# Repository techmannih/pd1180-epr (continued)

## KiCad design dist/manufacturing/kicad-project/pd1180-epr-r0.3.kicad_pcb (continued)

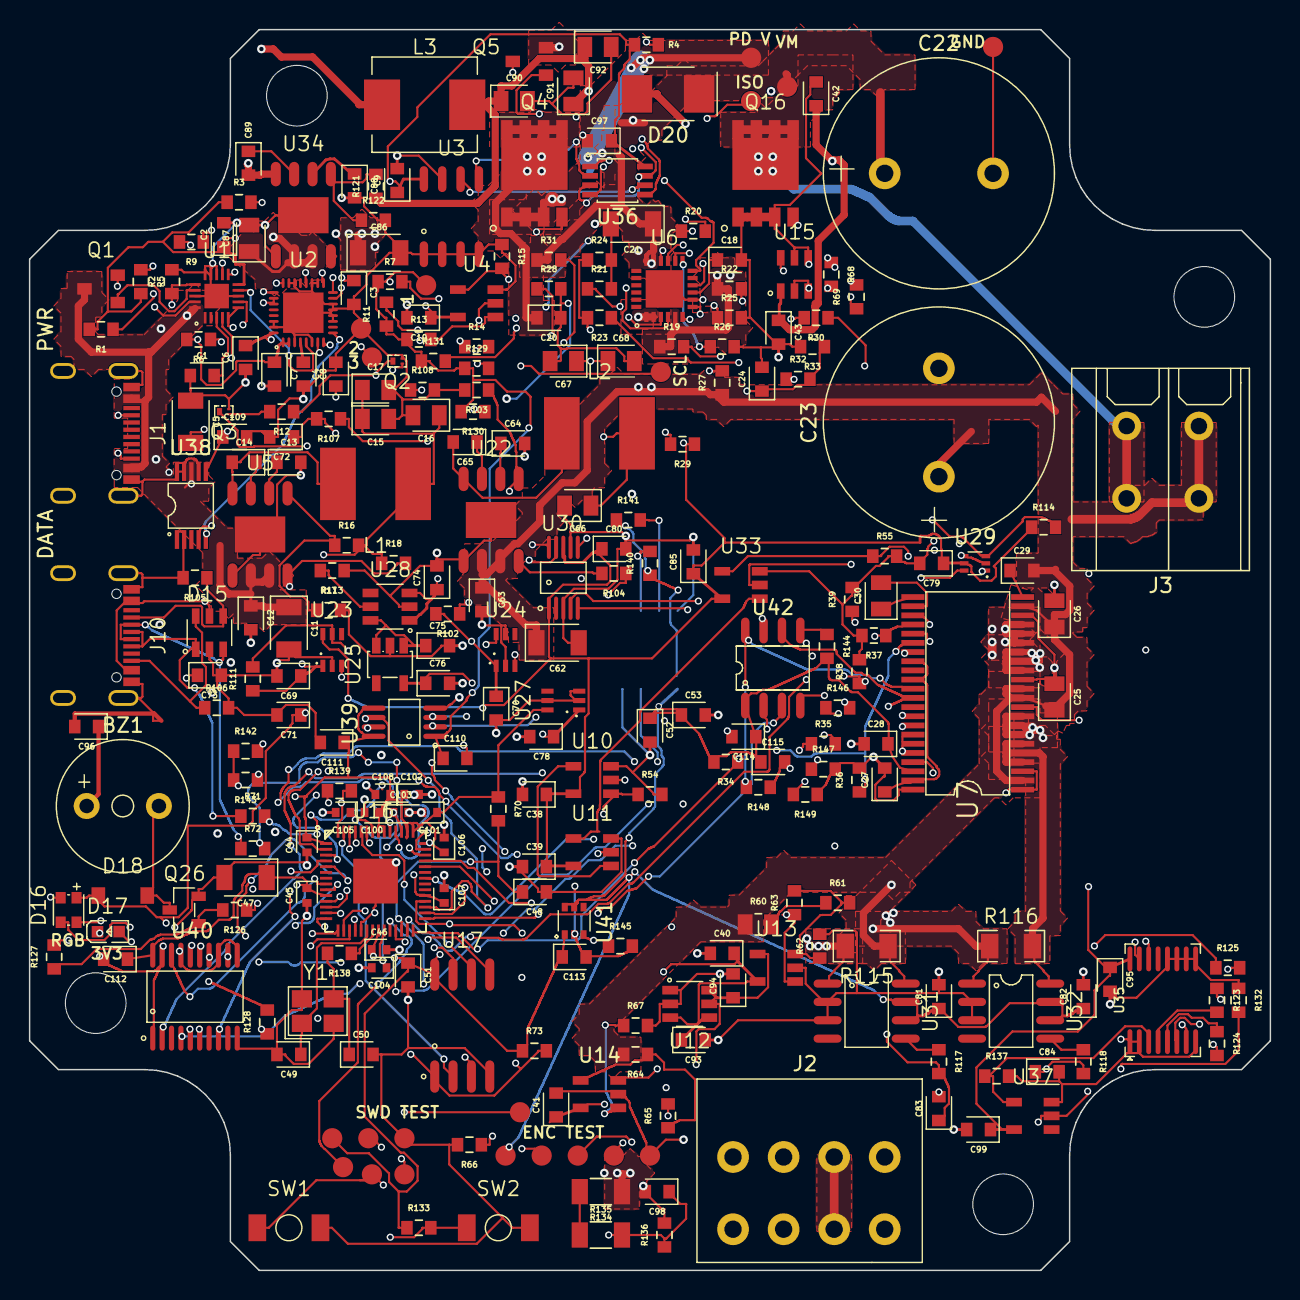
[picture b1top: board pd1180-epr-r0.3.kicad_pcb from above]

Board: 4 copper layers, 85.9 x 85.9 mm, 273 parts (1 on the bottom side), 158 nets.

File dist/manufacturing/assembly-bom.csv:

"Comment","Designator","Footprint","LCSC Part #","Quantity"
"USB4105-GF-A-060","J1,J10","SMD","C3025063","2"
"1M","R107","0603","C22935","1"
"47k","R108,R137","0603","C25819","2"
"100nF","C72,C9,C10,C14,C65,C69,C70,C24,C114,C38,C39,C89,C94,C40,C41,C43,C28,C48,C51,C73,C110,C111,C112,C74,C78,C109,C79,C80,C81,C82,C85,C99,C95,C97","0603","C14663","34"
"TPD4S480RUKR","U1","QFN-20(3x3)","C43131250","1"
"TPS26750SRSMR","U2","VQFN-32-EP(4x4)","C42166327","1"
"BSS123LT1G","Q1,Q5","SOT-23","C78755","2"
"100nF","C1,C12,C63,C20","0603","C15725","4"
"1uF","C2,C13,C64,C18,C115,C88,C93,C42,C27,C29,C113,C75","0603","C15849","12"
"220pF","C3,C4","0603","C106210","2"
"4.7uF","C5,C47","1206","C51205","2"
"10uF","C6,C7,C8,C71,C76,C96","0603","C96446","6"
"10k","R1,R14,R18,R104,R111,R21,R28,R29,R30,R148,R149,R54,R34,R35,R36,R37,R38,R39,R55,R70,R133,R73,R114,R131,R132","0603","C844918","25"
"100k","R2,R11,R13,R15,R16,R102,R121,R67,R69,R145,R113,R127","0603","C25803","12"
"M24512-RMN6TP","U3","SOIC-8","C79991","1"
"4.7k","R3,R4,R5,R6,R7,R22,R140,R141,R142,R143,R144,R128,R129,R130","0603","C23162","14"
"0","R9,R12","0603","C21189","2"
"CSD17484F4","Q2,Q3","PicoStar-3","C2862245","2"
"SN74LVC1G08DBVR","U4,U10,U11,U33","SOT-23-5","C7666","4"
"LMR36510ADDAR","U5,U22,U34","SOP-8-EP","C1858393","3"
"SWPA6045S220MT","L1,L2","SMD,6x6mm","C83454","2"
"2.2uF","C11,C62,C21,C86","1206","C170101","4"
"22uF","C15,C16,C17,C66,C67,C68,C90,C91,C92","0805","C45783","9"
"43.2k","R17,R103","0603","C137720","2"
"LM66100DCKR","U23,U24,U27","SC-70-6","C2869734","3"
"CSD19534Q5A","Q4,Q16","SON-8(5x6)","C114200","2"
"TPS26630RGER","U6","VQFN-24(4x4)","C1850276","1"
"180k","R19,R20,R31,R32","0603","C22827","4"
"422k","R23","0603","C705777","1"
"10k","R24,R62","0603","C95204","2"
"4.99k","R25","0603","C7293210","1"
"20k","R26,R33","0603","C4184","2"
"360k","R27","0603","C23146","1"
"EEUFS1J102","C22,C23","Plugin,D16xL25mm","C407979","2"
"MCP4822-E/SN","U42","SOIC-8","C16040","1"
"1.5k","R146,R147","0603","C22843","2"
"DRV8262DDVR","U7","HTSSOP-44","C33828788","1"
"2601-3104","J2","Plugin,P=3.5mm","C20252915","1"
"SRP7050TA-470M","L3","SMD,7.3x6.6mm","C2047110","1"
"9.09k","R122","0603","C861611","1"
"220nF","C87","0805","C513710","1"
"REF3425IDBVR","U12","SOT-23-6","C187836","1"
"TLV3201AIDBVR","U13,U14","SOT-23-5","C105188","2"
"180k","R60","0805","C351604","1"
"16.2k","R61","0603","C728583","1"
"1M","R63","0603","C326730","1"
"430k","R64","0603","C2984356","1"
"20k","R65","0603","C328424","1"
"1.2k","R66","0603","C5454462","1"
"UCC27511DBVR","U15","SOT-23-6","C191027","1"
"10","R68","0603","C22859","1"
"236-402","J3","Plugin","C3819425","1"
"SS10100","D20","SMBF","C49242208","1"
"4.7k","R134,R135","1206","C6675858","2"
"510","R136","0603","C7468460","1"
"10nF","C98,C83,C84","0603","C57112","3"
"100nF","C25,C26,C30","0805","C28233","3"
"100nF","C107,C106,C108,C100,C101,C104,C105,C44,C45,C46","0402","C1525","10"
"1uF","C102,C103","0402","C52923","2"
"1k","R138,R139,R117,R118,R123,R126","0603","C21190","6"
"RP2040","U16","LQFN-56(7x7)","C2040","1"
"27","R71,R72","0603","C25190","2"
"X322512MSB4SI","Y1","SMD3225-4P","C9002","1"
"33pF","C49,C50","0603","C1663","2"
"TS-1088-AR02016","SW1,SW2","SMD,4x3mm","C720477","2"
"W25Q32JVSSIM","U17","SOIC-8-208mil","C6000508","1"
"5.1k","R105,R106","0603","C23186","2"
"USBLC6-4SC6","D15","SOT-23-6L","C111212","1"
"TCA9517ADGKR","U39","VSSOP-8-0.65mm","C201698","1"
"SN74LVC244APWR","U40","TSSOP-20","C7668","1"
"TPS22919DCKR","U41","SC-70-6","C2149796","1"
"TPS2553DBVR","U28","SOT-23-6","C55266","1"
"TLV75533PDBVR","U25","SOT-23-5","C404027","1"
"TMP102AIDRLR","U29","SOT-563","C99269","1"
"ADS1115IDGSR","U30","VSSOP-10","C37593","1"
"INA237AIDGSR","U38","VSSOP-10-0.5mm","C2864837","1"
"INA240A1DR","U31,U32","SOIC-8","C2060769","2"
"FRM121WFR005TM","R115,R116","1206","C7419996","2"
"PCA9538PWR","U35","TSSOP-16","C201530","1"
"SN74LVC1G17DBVR","U37","SOT-23-5","C7836","1"
"NH-B2020RGBA-HF","D16","SMD,2.1x2.1mm","C2874116","1"
"FMB09A03-3V","BZ1","Plugin,D=9mm","C417385","1"
"AO3400A","Q26","SOT-23","C20917","1"
"XL-1608SURC-06","D17","0603","C965799","1"
"BAV21W-7-F","D18","SOD-123","C155214","1"
"330","R124,R125","0603","C23138","2"
"SN74LVC2G66DCTR","U36","MSOP-8","C2651913","1"

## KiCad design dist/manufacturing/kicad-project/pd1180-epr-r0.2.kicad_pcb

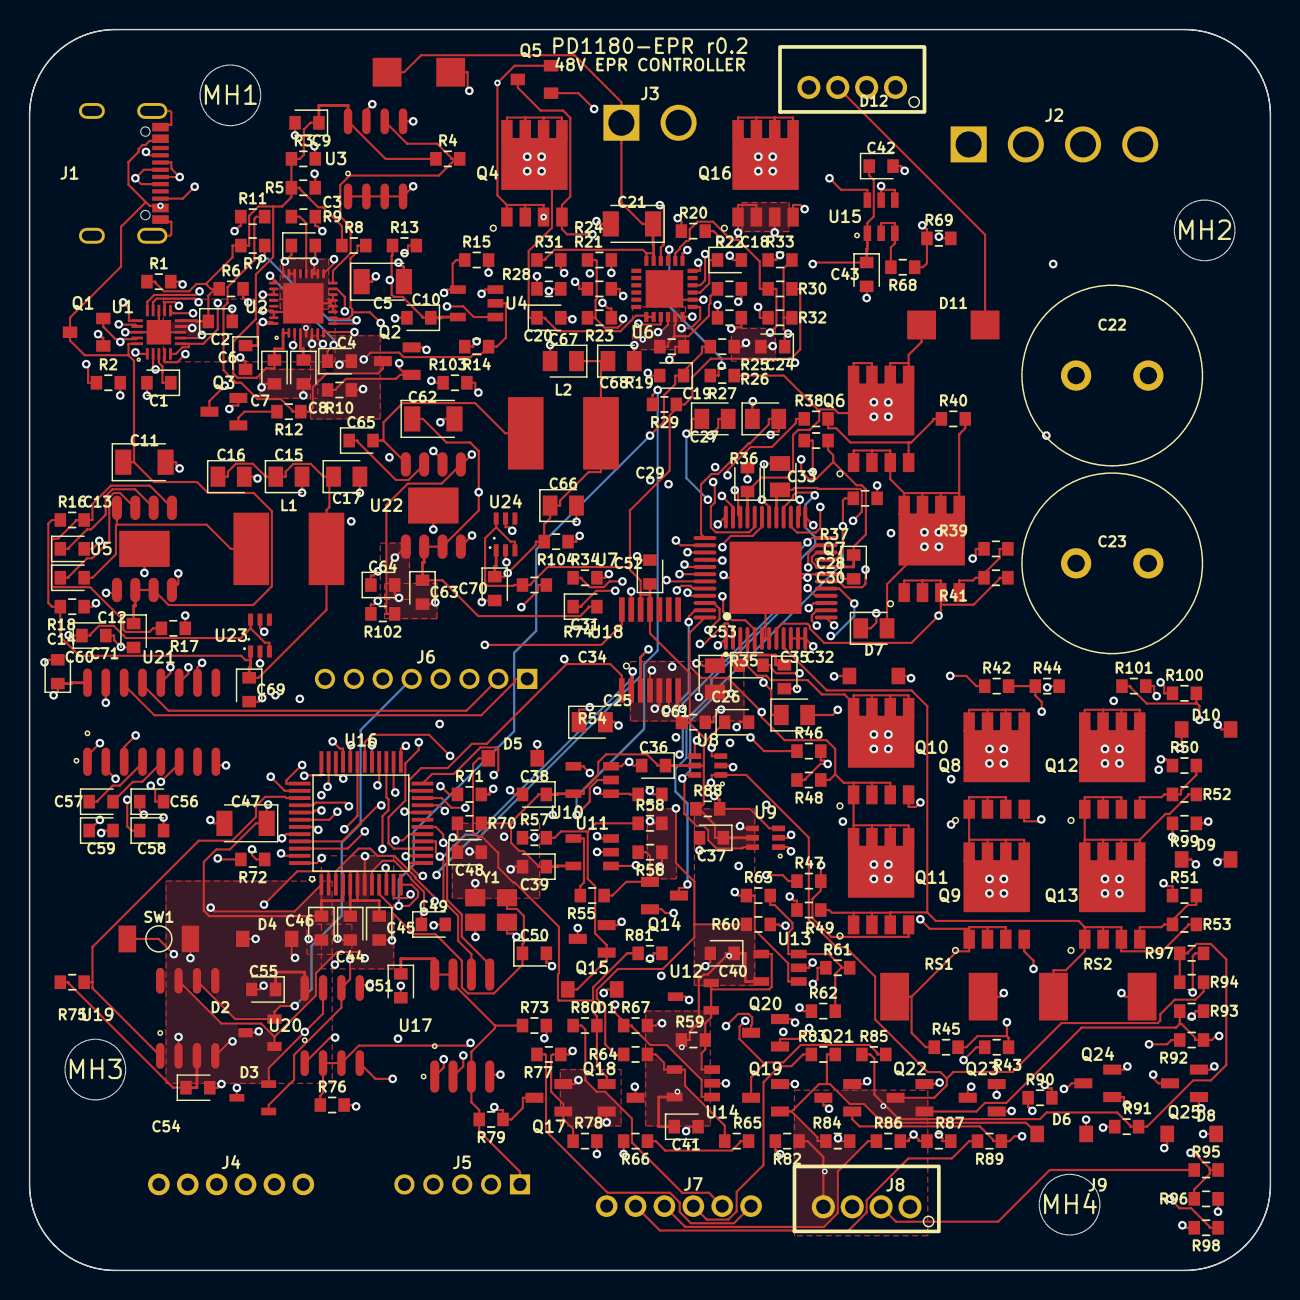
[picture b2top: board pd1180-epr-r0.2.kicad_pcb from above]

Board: 4 copper layers, 85.9 x 85.9 mm, 255 parts (0 on the bottom side), 177 nets.

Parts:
C1, C2, C9, C10, C12, C14, C18, C19, C20, C24, C28, C29, C31, C36, C37, C38, C39, C40, C41, C43, C44, C45, C46, C48, C51, C52, C54, C55, C56, C57, C58, C59, C60, C61, C63, C65, C69, C70: 100nF; capacitor_cap0603
C3, C4: 220pF; capacitor_cap0603
C5, C47: 4.7uF; capacitor_cap1206
C6, C7, C8, C71: 10uF; capacitor_cap0603
C11, C21, C62: 2.2uF; capacitor_cap1206
C13, C42, C53, C64: 1uF; capacitor_cap0603
C15, C16, C17, C66, C67, C68: 22uF; capacitor_cap0805
C22, C23: 470uF; EEUFR1J471
C25: 4.7uF; capacitor_cap0805
C26: 4.7uF; capacitor_cap0603
C27: 470nF; capacitor_cap0805
C30: 22nF; capacitor_cap0805
C32, C33, C34, C35: 220nF; capacitor_cap0805
C49, C50: 12pF; capacitor_cap0603
D1, D4, D5, D6, D7, D8, D9, D10: D; BAV21W-7-F
D2: SM24CANB-02HTG
D3: PSM712-LF-T7
D11, D12: D; SS110
J1: J1; USB4105-GF-A
J2: J2; B4P-VH_LF_SN
J3: J3; B2P-VH_LF_SN
J4: J4; B6B-PH-K-S_LF_SN
J5: J5; B5B-PH-K-S_LF_SN
J6: J6; B8B-PH-K-S_LF_SN
J7: J7; B6B-PH-K-S_LF_SN
J8: J8; B4B-PH-K-S_LF_SN
J9: J9; B4B-PH-K-S_LF_SN
L1, L2: 22µH; SWPA6045S220MT
MH1, MH2, MH3, MH4: hole_circle_holeDiameter4.2mm
Q1, Q5: BSS123LT1G
Q2, Q3, Q14, Q15, Q17, Q18, Q19, Q20, Q21, Q22, Q23, Q24, Q25: MMBT5551LT1G
Q4, Q6, Q7, Q8, Q9, Q10, Q11, Q12, Q13, Q16: CSD19534Q5A
R1, R11, R12, R13, R14, R18, R21, R24, R28, R29, R30, R35, R36, R37, R54, R56, R58, R62, R70, R73, R74, R75, R76, R78, R81, R84, R87, R90, R93, R96, R99, R101, R104: 10kΩ; resistor_res0603
R2, R9, R10, R15, R16, R40, R41, R44, R45, R48, R49, R52, R53, R57, R67, R69, R102: 100kΩ; resistor_res0603
R3, R4, R5, R6, R7, R8, R79, R82, R85, R88, R91, R94, R97: 4.7kΩ; resistor_res0603
R17, R103: 43.2kΩ; resistor_res0603
R19, R20, R31, R32, R60: 180kΩ; resistor_res0603
R22, R59: 220Ω; resistor_res0603
R23, R64: 430kΩ; resistor_res0603
R25: 4.02kΩ; resistor_res0603
R26, R33, R61, R65: 20kΩ; resistor_res0603
R27: 360kΩ; resistor_res0603
R34: 2.2Ω; resistor_res0603
R38, R39, R42, R43, R46, R47, R50, R51, R68: 10Ω; resistor_res0603
R55, R66, R98, R100: 1kΩ; resistor_res0603
R63: 1MΩ; resistor_res0603
R71, R72: 22Ω; resistor_res0603
R77, R80, R83, R86, R89, R92, R95: 47kΩ; resistor_res0603
RS1, RS2: HoLLR2512-3W-33mR-1%; HoLLR2512-3W-33mR-1
SW1: SW1; TS-1088-AR02016
U1: TPD4S480RUKR
U2: TPS26750SRSMR
U3: M24512-RMN6TP
U4, U10, U11: SN74LVC1G08DBVR
U5, U22: LMR36510ADDAR
U6: TPS26631RGER
U7: TMC5160A-TA-T
U8, U9: 74LVC1G157GW,125; 74LVC1G157GW_125
U12: TL431AIDBZR
U13, U14: TLV3201AIDBVR
U15: UCC27511DBVR
U16: STM32G0B1CBT6
U17: W25Q32JVSSIQ
U18: AS5047P-ATSM
U19: TCAN332DR
U20: MAX3485EESA+T; MAX3485EESA_T
U21: MAX3232ESE+T; MAX3232ESE_T
U23, U24: LM66100DCKR
Y1: Y1; X322516MLB4SI

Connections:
BLOCK_FAST_GATE: Q5.1, U6.4
BLOCK_GATE: Q4.4, Q5.3, U6.3
BOOT_A1: C32.1, U7.42
BOOT_A2: C33.1, U7.35
BOOT_B1: C34.1, U7.2
BOOT_B2: C35.1, U7.43
BRAKE_DRIVE: R68.1, U15.2, U15.3
BRAKE_GATE: Q16.4, R68.2, R69.1
BRAKE_MID: R60.2, R61.1
BRAKE_ON: R63.1, U13.1, U15.6
BRAKE_RETURN: J3.2, Q16.5, Q16.6, Q16.7, Q16.8, Q16.9
BRAKE_SENSE: R61.2, R62.1, R63.2, U13.3
BUCK_BOOT: C14.1, U5.7
BUCK_FB: R16.2, R17.1, U5.5
BUCK_SW: C14.2, L1.1, U5.8
BUCK_VCC: C13.1, U5.6
CAN_H: D2.1, J6.4, U19.7
CAN_L: D2.2, J6.5, U19.6
CAN_RX: U16.38, U19.4
CAN_TX: R75.2, U16.39, U19.1
CC1_CONN: J1.15, U1.4, U1.7
CC1_PD: C3.1, U1.12, U2.24
CC2_CONN: J1.9, U1.5, U1.6
CC2_PD: C4.1, U1.11, U2.25
CC_FAULT_N: R1.2, U1.9, U2.5
CC_VBIAS: C1.1, U1.3
DIN0: Q17.3, R79.2, U16.2
DIN0_24V: J7.1, R77.1
DIN0_BASE: D4.1, Q17.1, R77.2, R78.1
DIN1: Q18.3, R82.2, U16.3
DIN1_24V: J7.2, R80.1
DIN1_BASE: D5.1, Q18.1, R80.2, R81.1
DIR_24V: J8.2, R95.1
DIR_IN: Q23.3, R97.2, U9.1, U16.31
DIR_IN_BASE: D10.1, Q23.1, R95.2, R96.1
DRV_EN_N: Q14.3, R37.2, U7.28
EEP_IRQ_N: R5.2, U2.17
EEP_SCL: R4.2, U2.16, U3.6
EEP_SDA: R3.2, U2.15, U3.5
EFUSE_EN: R15.1, U4.4, U6.12
EFUSE_FAULT_N: R30.2, U6.14, U16.21
EFUSE_IN: C20.1, Q4.5, Q4.6, Q4.7, Q4.8, Q4.9, U6.1, U6.2
ENABLE_CHAIN: Q14.2, Q15.3
ENC_A: J5.2, U7.24, U18.7
ENC_B: J5.3, U7.23, U18.6
ENC_CS_N: R74.2, U16.23, U18.1
ENC_I: J5.4, U7.25, U18.14
EPR_BLK_GATE: Q1.1, U1.17
EPR_EN: R2.1, U1.16, U2.7
FLASH_CS_N: R73.2, U16.24, U17.1
GH_A1: Q6.4, R38.2, R40.1
GH_A1_DRV: R38.1, U7.41
GH_A2: Q8.4, R42.2, R44.1
GH_A2_DRV: R42.1, U7.36
GH_B1: Q10.4, R46.2, R48.1
GH_B1_DRV: R46.1, U7.1
GH_B2: Q12.4, R50.2, R52.1
GH_B2_DRV: R50.1, U7.44
GL_A1: Q7.4, R39.2, R41.1
GL_A1_DRV: R39.1, U7.39
GL_A2: Q9.4, R43.2, R45.1
GL_A2_DRV: R43.1, U7.38
GL_B1: Q11.4, R47.2, R49.1
GL_B1_DRV: R47.1, U7.47
GL_B2: Q13.4, R51.2, R53.1
GL_B2_DRV: R51.1, U7.46
GND: C1.2, C2.2, C3.2, C4.2, C5.2, C6.2, C7.2, C8.2, C9.2, C10.2, C11.2, C12.2, C13.2, C15.2, C16.2, C17.2, C18.2, C19.2, C20.2, C21.2, C22.2, C23.2, C24.2, C25.2, C26.2, C27.2, C28.2, C29.2, C36.2, C37.2, C38.2, C39.2, C40.2, C41.2, C42.2, C43.2, C44.2, C45.2, C46.2, C47.2, C48.2, C49.2, C50.2, C51.2, C52.2, C53.2, C54.2, C55.2, C58.2, C59.2, C60.2, C61.2, C62.2, C63.2, C64.2, C66.2, C67.2, C68.2, C69.2, C70.2, C71.2, D1.2, D2.3, D3.3, D4.2, D5.2, D6.2, D7.2, D8.2, D9.2, D10.2, J1.1, J1.2, J1.3, J1.4, J1.5, J1.6, J1.19, J1.20, J4.3, J5.5, J6.3, J6.6, J7.6, J8.3, Q2.2, Q3.2, Q15.2, Q16.1, Q16.2, Q16.3, Q17.2, Q18.2, Q19.2, Q20.2, Q21.2, Q22.2, Q23.2, Q24.2, Q25.2, R2.2, R10.2, R14.2, R15.2, R17.2, R21.2, R24.2, R25.2, R26.2, R28.2, R33.2, R36.2, R54.2, R56.2, R58.2, R62.2, R66.2, R67.2, R69.2, R76.2, R78.2, R81.2, R84.2, R87.2, R90.2, R93.2, R96.2, R99.2, R101.2, R103.2, RS1.2, RS2.2, SW1.2, U1.8, U1.13, U1.18, U1.21, U2.3, U2.6, U2.11, U2.12, U2.13, U2.14, U2.18, U2.19, U2.22, U2.23, U2.30, U2.31, U2.33, U3.1, U3.2, U3.3, U3.4, U3.7, U4.3, U5.1, U5.9, U6.8, U6.25, U7.6, U7.7, U7.10, U7.11, U7.12, U7.19, U7.30, U7.49, U8.2, U9.2, U10.3, U11.3, U12.3, U13.2, U14.2, U15.4, U15.5, U16.7, U17.4, U18.5, U18.13, U19.2, U20.5, U21.8, U21.10, U21.15, U22.1, U22.9, U23.2, U23.5, U24.2, U24.5, Y1.2, Y1.4
HOME_24V: J7.5, R89.1
HOME_IN: Q21.3, R91.2, U16.27
HOME_IN_BASE: D8.1, Q21.1, R89.2, R90.1
HW_ENABLE_24V: J9.2, R57.1
HW_ENABLE_BASE: D1.1, Q15.1, R57.2, R58.1
IIN_MON: C19.1, R26.1, U6.13, U16.12
ILIM_SET: R25.1, U6.10
LOGIC_PG: R18.2, U5.4
MCU_RUN: R54.1, U10.1, U16.37
MOTOR_A1: C32.2, J2.1, Q6.1, Q6.2, Q6.3, Q7.5, Q7.6, Q7.7, Q7.8, Q7.9, R40.2, U7.40
MOTOR_A2: C33.2, J2.2, Q8.1, Q8.2, Q8.3, Q9.5, Q9.6, Q9.7, Q9.8, Q9.9, R44.2, U7.37
MOTOR_B1: C34.2, J2.3, Q10.1, Q10.2, Q10.3, Q11.5, Q11.6, Q11.7, Q11.8, Q11.9, R48.2, U7.48
MOTOR_B2: C35.2, J2.4, Q12.1, Q12.2, Q12.3, Q13.5, Q13.6, Q13.7, Q13.8, Q13.9, R52.2, U7.45
MOTOR_BUCK_BOOT: C65.1, U22.7
MOTOR_BUCK_FB: R102.2, R103.1, U22.5
MOTOR_BUCK_SW: C65.2, L2.1, U22.8
MOTOR_BUCK_VCC: C64.1, U22.6
MOTOR_LOGIC_PG: R104.2, U22.4
MOTOR_OVP_LOW: R65.2, R66.1
MOTOR_OVP_SENSE: R64.2, R65.1, U14.4
MOTOR_PG: R29.2, U6.16, U10.2, U16.43
NRST: C48.1, J4.5, R70.2, SW1.1, U16.10
OSC_IN: C49.1, U16.8, Y1.1
OSC_OUT: C50.1, U16.9, Y1.3
OUT0: D11.2, J9.3, Q24.3
OUT0_BASE: Q24.1, R98.2, R99.1
OUT0_DRIVE: R98.1, U16.40
OUT1: D12.2, J9.4, Q25.3
OUT1_BASE: Q25.1, R100.2, R101.1
OUT1_DRIVE: R100.1, U16.41
OVP_DIV: R23.2, R24.1, U6.7
OVP_TOP: R22.2, R23.1
PD_1V5: C8.1, U2.4
PD_3V3: C2.1, C7.1, C9.1, R1.1, R3.1, R4.1, R5.1, R6.1, R7.1, R8.1, U1.10, U2.1, U2.2, U3.8
PD_INV_BASE: Q3.1, R12.2
PD_IRQ_N: R8.2, U2.10, U16.20
PD_LEVEL_BASE: Q2.1, R9.2, R10.1
PD_PATH_HV: R9.1, U2.20
PD_PATH_N: Q2.3, R11.2, R12.1
PD_PATH_OK: Q3.3, R13.2, U4.1
PD_SCL: R7.2, U2.9, U16.45
PD_SDA: R6.2, U2.8, U16.46
PG_DIV: R27.2, R28.1, U6.15
POWER_PERMIT: R14.1, U4.2, U16.44
REFL_STEP: U7.17, U8.4
REFR_DIR: U7.18, U9.4
RS232_C1N: C56.2, U21.3
RS232_C1P: C56.1, U21.1
RS232_C2N: C57.2, U21.5
RS232_C2P: C57.1, U21.4
RS232_RX: U16.32, U21.12
RS232_RX_CONN: J6.2, U21.13
RS232_TX: U16.29, U21.11
RS232_TX_CONN: J6.1, U21.14
RS232_VN: C59.1, U21.6
RS232_VP: C58.1, U21.2
RS485_A: D3.1, J6.7, U20.6
RS485_B: D3.2, J6.8, U20.7
RS485_DE: R76.1, U16.22, U20.2, U20.3
RS485_RX: U16.14, U20.1
RS485_TX: U16.13, U20.4
RUN_BASE: Q14.1, R55.2, R56.1
RUN_PG: U10.4, U11.1
RUN_SAFE: R55.1, U11.4
SD_MODE: R36.1, U7.21, U8.6, U9.6, U16.28
SENSE_A: Q7.1, Q7.2, Q7.3, Q9.1, Q9.2, Q9.3, R41.2, R45.2, RS1.1, U7.8
SENSE_B: Q11.1, Q11.2, Q11.3, Q13.1, Q13.2, Q13.3, R49.2, R53.2, RS2.1, U7.9
SLEW_CAP: C18.1, U6.9
SPI_MISO: U7.16, U16.17, U17.2, U18.3
SPI_MOSI: U7.15, U16.18, U17.5, U18.4
SPI_SCK: U7.14, U16.16, U17.6, U18.2
STATUS_GPIO: J4.6, U16.1
STEP_24V: J8.1, R92.1
STEP_IN: Q22.3, R94.2, U8.1, U16.30
STEP_IN_BASE: D9.1, Q22.1, R92.2, R93.1
STOPL_24V: J7.3, R83.1
STOPR_24V: J7.4, R86.1
STOP_L: Q19.3, R85.2, U8.3, U16.25
STOP_L_BASE: D6.1, Q19.1, R83.2, R84.1
STOP_R: Q20.3, R88.2, U9.3, U16.26
STOP_R_BASE: D7.1, Q20.1, R86.2, R87.1
SWCLK: J4.4, U16.36
SWDIO: J4.2, U16.35
TMC_5V: C26.1, R34.1, U7.5
TMC_12V: C25.1, C42.1, C43.1, U7.3, U15.1
TMC_CPI: C30.2, U7.32
TMC_CPO: C30.1, U7.31
TMC_CS_N: R35.2, U7.13, U16.15
TMC_DIAG0: U7.26, U16.42
TMC_DIAG1: U7.27, U16.47
TMC_VCC: C27.1, R34.2, U7.29
TMC_VCP: C31.1, U7.34
USB_DM: R72.2, U16.33
USB_DM_CONN: J1.12, J1.14, U1.2
USB_DM_PROTECTED: R72.1, U1.14
USB_DP: R71.2, U16.34
USB_DP_CONN: J1.11, J1.13, U1.1
USB_DP_PROTECTED: R71.1, U1.15
USB_VBUS: C11.1, C12.1, J1.7, J1.8, J1.17, J1.18, Q1.3, Q4.1, Q4.2, Q4.3, Q5.2, R19.1, R22.1, U1.20, U5.2, U5.3, U6.5
UVLO_DIV: R20.2, R21.1, U6.6
UVLO_MID: R19.2, R20.1
V3V3: C6.1, C10.1, C28.1, C36.1, C37.1, C38.1, C39.1, C40.1, C41.1, C44.1, C45.1, C46.1, C47.1, C51.1, C52.1, C53.1, C54.1, C55.1, C60.1, C71.1, J4.1, J5.1, J8.4, R11.1, R13.1, R29.1, R30.1, R35.1, R37.1, R59.1, R70.1, R73.1, R74.1, R75.1, R79.1, R82.1, R85.1, R88.1, R91.1, R94.1, R97.1, U2.32, U4.5, U7.20, U7.22, U8.5, U9.5, U10.5, U11.5, U13.5, U14.5, U16.4, U16.5, U16.6, U17.3, U17.7, U17.8, U18.11, U18.12, U19.3, U20.8, U21.16, U23.3, U23.6, U24.3, U24.6
V3V3_MOTOR: C66.1, C67.1, C68.1, C70.1, L2.2, R102.1, R104.1, U24.1
V3V3_USB: C15.1, C16.1, C17.1, C69.1, L1.2, R16.1, R18.1, U23.1
VBUS_LV: C5.1, Q1.2, U1.19, U2.26, U2.27
VMON_ADC: C24.1, R32.2, R33.1, U16.11
VMON_MID: R31.2, R32.1
VMOTOR: C21.1, C22.1, C23.1, C29.1, C31.2, C61.1, C62.1, C63.1, D11.1, D12.1, J3.1, J9.1, Q6.5, Q6.6, Q6.7, Q6.8, Q6.9, Q8.5, Q8.6, Q8.7, Q8.8, Q8.9, Q10.5, Q10.6, Q10.7, Q10.8, Q10.9, Q12.5, Q12.6, Q12.7, Q12.8, Q12.9, R27.1, R31.1, R60.1, R64.1, U6.17, U6.18, U7.4, U7.33, U22.2, U22.3
VMOTOR_OK: R67.1, U11.2, U14.1, U16.48
VREF_2V495: R59.2, U12.1, U12.2, U13.4, U14.3
